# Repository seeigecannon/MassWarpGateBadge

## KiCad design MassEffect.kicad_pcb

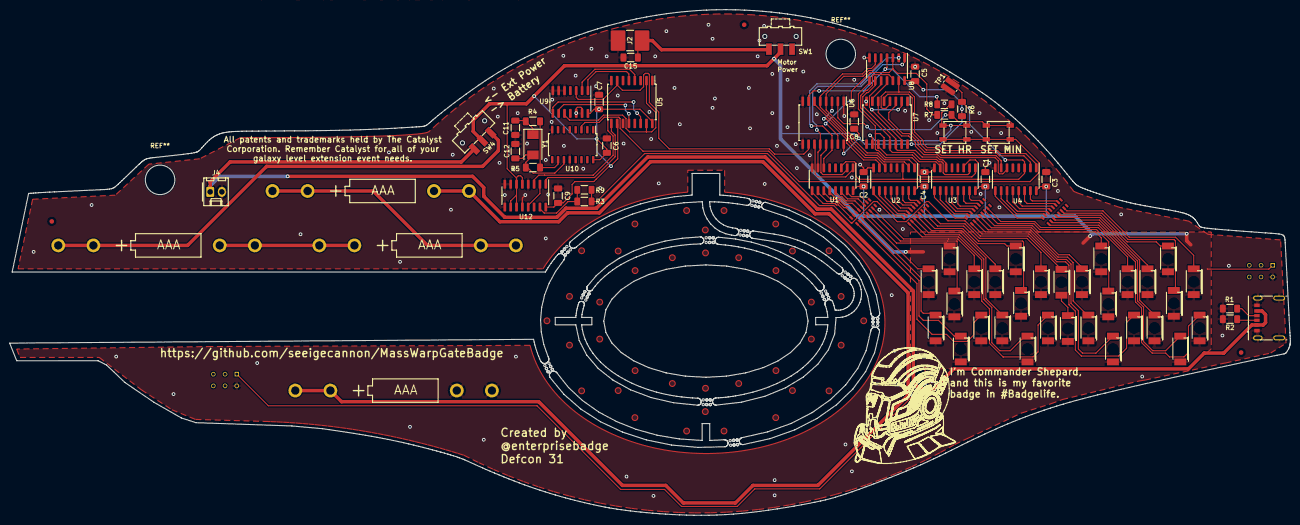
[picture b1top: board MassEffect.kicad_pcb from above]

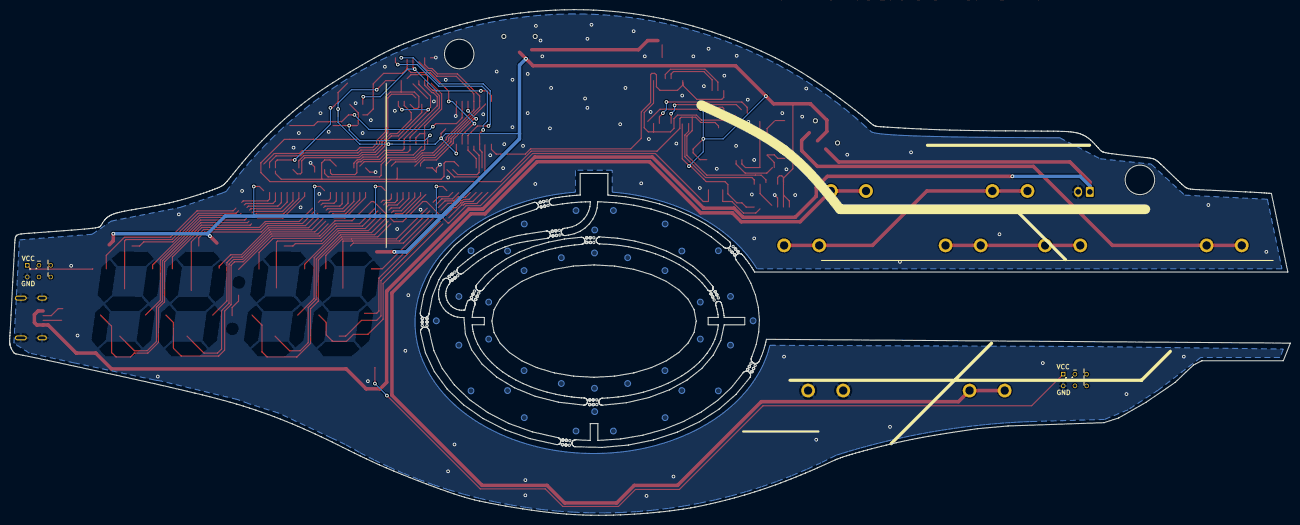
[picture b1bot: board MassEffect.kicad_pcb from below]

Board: 2 copper layers, 277.9 x 109.7 mm, 85 parts (3 on the bottom side), 104 nets.

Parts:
BT1, BT2, BT3, BT4: AAA Holder; BK-82
C1, C2, C3, C4, C5, C6, C7, C8, C9, C15: .1uF; C_1206_3216Metric_Pad1.33x1.80mm_HandSolder
C11, C12: 33pF; C_1206_3216Metric_Pad1.33x1.80mm_HandSolder
D1, D2: LED; LED_PLCC_flipped
DA1, DA2, DA3, DA4: LED; LED_PLCC_flipped
DB1, DB2, DB3, DB4: LED; LED_PLCC_flipped
DC1, DC2, DC3, DC4: LED; LED_PLCC_flipped
DD1, DD2, DD3, DD4: LED; LED_PLCC_flipped
DE1, DE2, DE3, DE4: LED; LED_PLCC_flipped
DF1, DF2, DF3, DF4: LED; LED_PLCC_flipped
DG1, DG2, DG3, DG4: LED; LED_PLCC_flipped
FID1: 7segmentPattern; 7segPattern
FID2, FID3, FID4: Fiducial; Fiducial_1mm_Mask2mm
J2: Conn_02x01; R_2816_7142Metric_Pad3.20x4.45mm_HandSolder
J4: Conn_02x01; Molex_KK-254_AE-6410-02A_1x02_P2.54mm_Vertical
J5, J6: SAO; SAO_BadgelifeConnector
J7: Ext Power; USB_C_thin_10164359-00011LF
R1, R2: 5.1k; R_1206_3216Metric_Pad1.30x1.75mm_HandSolder
R3, R6, R7, R8, R9: 1k; R_1206_3216Metric_Pad1.30x1.75mm_HandSolder
R4: 300k; R_1206_3216Metric_Pad1.30x1.75mm_HandSolder
R5: 10M; R_1206_3216Metric_Pad1.30x1.75mm_HandSolder
RN1, RN2, RN3, RN4: R_Pack08; R_Array_Convex_8x2506
SW1: Motor; SW_SPDT_CK-JS102011SAQN
SW2: Hour; 4.5mm switch
SW3: Minute; 4.5mm switch
SW4: SW_SPDT; SW_SPDT_CK-JS102011SAQN
TP1: Test LEDs; R_0612_1632Metric_Pad1.18x3.40mm_HandSolder
U1, U2, U3, U4: 74LS247; SOIC-16_3.9x9.9mm_P1.27mm
U5, U6, U7: MC14520B; SOIC-16W_7.5x10.3mm_P1.27mm
U8, U9: 4081; SOIC-14_3.9x8.7mm_P1.27mm
U10: SOIC-16_4.55x10.3mm_P1.27mm
U12: 4027; SOIC-16_3.9x9.9mm_P1.27mm
Y1: 32.768kHz; Crystal_SMD_0603-2Pin_6.0x3.5mm

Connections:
/1 hour/A: U3.7 (A), U7.11 (Q0)
/1 hour/B: U3.1 (B), U7.12 (Q1), U8.8
/1 hour/C: U3.2 (C), U7.13 (Q2), U8.12
/1 hour/D: U3.6 (D), U7.14 (Q3), U8.9
/1 minute/A: U1.7 (A), U6.12 (Q1), U8.1
/1 minute/B: U1.1 (B), U6.11 (Q0)
/1 minute/C: U1.2 (C), U6.13 (Q2)
/1 minute/D: U1.6 (D), U6.14 (Q3), U8.2
/10 hour/A: U4.7 (A), U7.3 (Q0)
/10 hour/B: U4.1 (B), U7.4 (Q1), U8.13
/10 hour/C: U4.2 (C), U7.5 (Q2)
/10 hour/D: U4.6 (D), U7.6 (Q3)
/10 minute/A: U2.7 (A), U6.3 (Q0)
/10 minute/B: U2.1 (B), U6.4 (Q1), U8.5
/10 minute/C: U2.2 (C), U6.5 (Q2), U8.6
/10 minute/D: U2.6 (D), U6.6 (Q3)
/Signal Generators/1Hz Clock: U5.9 (CLK), U12.1 (Q)
/Signal Generators/1/2 Hz Clock: R3.1, R9.1, U12.15 (Q)
/Signal Generators/2Hz: SW2.1 (A), SW3.1 (A), U10.3 (Q14), U12.3 (CK)
GND: BT2.2 (-), C1.2, C2.2, C3.2, C4.2, C5.2, C6.2, C7.2, C8.2, C9.2, C11.2, C12.2, C15.2, J2.2, J4.2, J5.2, J6.2, J7.A12 (GND), J7.B12 (GND), J7.S1 (SHIELD), R1.2, R2.2, TP1.1, U1.8 (GND), U2.8 (GND), U3.8 (GND), U4.8 (GND), U5.1 (CLK), U5.8 (GND), U6.1 (CLK), U6.8 (GND), U6.9 (CLK), U7.1 (CLK), U7.8 (GND), U7.9 (CLK), U8.7 (VSS), U9.5, U9.6, U9.7 (VSS), U9.12, U9.13, U10.8 (GND), U10.12 (CT=0), U12.4 (R), U12.7 (S), U12.8 (VSS), U12.9 (S), U12.12 (R)
unnamed: BT1.1 (+), BT3.2 (-)
unnamed: BT1.2 (-), BT2.1 (+)
unnamed: BT3.1 (+), BT4.2 (-)
unnamed: BT4.1 (+), SW4.1 (A)
unnamed: C11.1, R4.2, Y1.1
unnamed: D1.1 (K), D2.2 (A)
unnamed: D2.1 (K), R3.2, R9.2
unnamed: DA1.1 (K), RN1.5 (R5.1)
unnamed: DA2.1 (K), RN2.5 (R5.1)
unnamed: DA3.1 (K), RN3.5 (R5.1)
unnamed: DA4.1 (K), RN4.5 (R5.1)
unnamed: DB1.1 (K), RN1.4 (R4.1)
unnamed: DB2.1 (K), RN2.4 (R4.1)
unnamed: DB3.1 (K), RN3.4 (R4.1)
unnamed: DB4.1 (K), RN4.4 (R4.1)
unnamed: DC1.1 (K), RN1.3 (R3.1)
unnamed: DC2.1 (K), RN2.3 (R3.1)
unnamed: DC3.1 (K), RN3.3 (R3.1)
unnamed: DC4.1 (K), RN4.3 (R3.1)
unnamed: DD1.1 (K), RN1.2 (R2.1)
unnamed: DD2.1 (K), RN2.2 (R2.1)
unnamed: DD3.1 (K), RN3.2 (R2.1)
unnamed: DD4.1 (K), RN4.2 (R2.1)
unnamed: DE1.1 (K), RN1.1 (R1.1)
unnamed: DE2.1 (K), RN2.1 (R1.1)
unnamed: DE3.1 (K), RN3.1 (R1.1)
unnamed: DE4.1 (K), RN4.1 (R1.1)
unnamed: DF1.1 (K), RN1.7 (R7.1)
unnamed: DF2.1 (K), RN2.7 (R7.1)
unnamed: DF3.1 (K), RN3.7 (R7.1)
unnamed: DF4.1 (K), RN4.7 (R7.1)
unnamed: DG1.1 (K), RN1.6 (R6.1)
unnamed: DG2.1 (K), RN2.6 (R6.1)
unnamed: DG3.1 (K), RN3.6 (R6.1)
unnamed: DG4.1 (K), RN4.6 (R6.1)
unnamed: C15.1, J2.1, SW1.3 (C)
unnamed: J4.1, J7.A9 (VBUS), J7.B9 (VBUS), SW4.3 (C)
unnamed: J7.A5 (CC1), R2.1
unnamed: J7.B5 (CC2), R1.1
unnamed: RN1.16 (R1.2), U1.9 (e)
unnamed: RN1.15 (R2.2), U1.10 (d)
unnamed: RN1.14 (R3.2), U1.11 (c)
unnamed: RN1.13 (R4.2), U1.12 (b)
unnamed: RN1.12 (R5.2), U1.13 (a)
unnamed: RN1.11 (R6.2), U1.14 (g)
unnamed: RN1.10 (R7.2), U1.15 (f)
unnamed: RN2.16 (R1.2), U2.9 (e)
unnamed: RN2.15 (R2.2), U2.10 (d)
unnamed: RN2.14 (R3.2), U2.11 (c)
unnamed: RN2.13 (R4.2), U2.12 (b)
unnamed: RN2.12 (R5.2), U2.13 (a)
unnamed: RN2.11 (R6.2), U2.14 (g)
unnamed: RN2.10 (R7.2), U2.15 (f)
unnamed: RN3.16 (R1.2), U3.9 (e)
unnamed: RN3.15 (R2.2), U3.10 (d)
unnamed: RN3.14 (R3.2), U3.11 (c)
unnamed: RN3.13 (R4.2), U3.12 (b)
unnamed: RN3.12 (R5.2), U3.13 (a)
unnamed: RN3.11 (R6.2), U3.14 (g)
unnamed: RN3.10 (R7.2), U3.15 (f)
unnamed: RN4.16 (R1.2), U4.9 (e)
unnamed: RN4.15 (R2.2), U4.10 (d)
unnamed: RN4.14 (R3.2), U4.11 (c)
unnamed: RN4.13 (R4.2), U4.12 (b)
unnamed: RN4.12 (R5.2), U4.13 (a)
unnamed: RN4.11 (R6.2), U4.14 (g)
unnamed: RN4.10 (R7.2), U4.15 (f)
unnamed: R8.1, SW2.2 (B), U7.10 (EN)
unnamed: R7.1, SW3.2 (B), U6.2 (EN)
unnamed: U5.2 (EN), U5.15 (RST), U9.10
unnamed: U5.4 (Q1), U9.2
unnamed: U5.5 (Q2), U9.1
unnamed: U5.7 (RST), U6.10 (EN), U9.3
unnamed: U5.12 (Q1), U9.9
unnamed: U5.14 (Q3), U9.8
unnamed: R8.2, U6.7 (RST), U8.4
unnamed: R7.2, U6.15 (RST), U8.3
unnamed: U7.2 (EN), U7.15 (RST), U8.10
unnamed: U7.7 (RST), U8.11
unnamed: C12.1, R5.2, U10.11 (RCX), Y1.2
unnamed: R4.1, R5.1, U10.10 (RX)
unnamed: U12.2 (~Q), U12.13 (CK)
VCC: C1.1, C2.1, C3.1, C4.1, C5.1, C6.1, C7.1, C8.1, C9.1, D1.2 (A), DA1.2 (A), DA2.2 (A), DA3.2 (A), DA4.2 (A), DB1.2 (A), DB2.2 (A), DB3.2 (A), DB4.2 (A), DC1.2 (A), DC2.2 (A), DC3.2 (A), DC4.2 (A), DD1.2 (A), DD2.2 (A), DD3.2 (A), DD4.2 (A), DE1.2 (A), DE2.2 (A), DE3.2 (A), DE4.2 (A), DF1.2 (A), DF2.2 (A), DF3.2 (A), DF4.2 (A), DG1.2 (A), DG2.2 (A), DG3.2 (A), DG4.2 (A), J5.1, J6.1, R6.1, SW1.2 (B), SW4.2 (B), U1.16 (VCC), U2.16 (VCC), U3.16 (VCC), U4.16 (VCC), U5.10 (EN), U5.16 (VCC), U6.16 (VCC), U7.16 (VCC), U8.14 (VDD), U9.14 (VDD), U10.16 (VCC), U12.5 (K), U12.6 (J), U12.10 (J), U12.11 (K), U12.16 (VDD)
testLEDs: R6.2, TP1.2, U1.3 (Lt), U2.3 (Lt), U3.3 (Lt), U4.3 (Lt)

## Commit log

2023-08-11 Add files via upload
    Initial release. Will do a writeup later.
2023-08-11 Add files via upload
    Added gerbers
2023-08-11 Added Fusion 360 files
